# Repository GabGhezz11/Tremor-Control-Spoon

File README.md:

# Description

An electronic Tremor Control Spoon designed to compensate involuntary hand
tremors in Parkinson's disease patients during meals, developed as part of the
Biodesign course at Università Campus Bio-Medico di Roma in 2023 by a team of 10 students.

---

## Overview

This project focused on the design and development of an electronically
stabilized spoon to assist individuals with Parkinson's disease by compensating
tremors during meal consumption, promoting greater independence and comfort in
daily life. The work was developed in collaboration with a team of colleagues,
with my contribution made remotely while based in Vienna.

The device integrates mechanical, electronic, and control system design:

- **Sensing**: an IMU sensor (MPU-6050) for real-time motion tracking
  (acceleration and angular velocity)
- **Control**: an ATMega328-MUR microcontroller processes sensor data through a
  complementary filter to estimate roll and pitch angles
- **Actuation**: dual servo motors compensate roll and pitch tremors in real
  time, with compensation limited to ±30° on both axes to preserve natural
  eating motion

## Repository Structure

- `firmware/` — Arduino/C firmware implementing the sense-plan-act control loop
  - `TCS_control.ino` — main Arduino sketch
  - `Functions.c` — control and filtering functions
  - `Variables.h` — shared variable/constant definitions
- `electronics/` — PCB design and documentation (Eagle CAD)
  - `scheda_progetto_ver_4.2.sch` — schematic
  - `scheda_progetto_ver_4.2.brd` — board layout
  - `BoM_ver4.2.xlsx` — bill of materials
  - `scheda_progetto_ver_4` — project/design documentation
- `cad/` — Mechanical design files (Solid Edge/STEP) for the handle, motor
  case, and spoon tool
  - `.step Files/` — final STEP files, importable in any CAD software
  - `Drafts/` — intermediate/working Solid Edge design iterations
- `data-analysis/` — MATLAB scripts used to extract tremor frequency and
  acceleration/angular velocity ranges from a reference Parkinsonian tremor
  dataset, informing sensor and motor specifications

## Design Highlights

**Mechanical**: modeled in Solid Edge and based on anthropometric hand data
from adult users, optimized for usability, compactness, and dishwasher-safe
cleaning. Made of polypropylene (biocompatible, heat-resistant, dishwasher-safe)
with silicon caps for the removable USB/charging ports.

**Electronics**: sensing, control, and power supply modules integrated onto a
single miniaturized PCB (57 x 31 mm, a 10% area reduction from the original
demo stripboard), powered by a 2S1P LiPo battery (800 mAh, 7.4 V), with voltage
regulation and USB communication circuits.

**Firmware**: a complementary filter combines accelerometer and gyroscope data
to estimate roll and pitch angles, driving the servos to counteract tremor in
real time while allowing intentional tilting (e.g., to scoop food).

## Personal Contribution - Matlab Data Analysis

The analysis focused on two tremor-related tasks from the reference dataset:

- **Kinetic tremor (task AS316)**: analyzed to extract the acceleration and
  angular velocity ranges during a spoon-eating-like motion.
- **Postural tremor (task AS315)**: analyzed to identify the maximum and
  dominant frequencies of the Parkinsonian tremor signal.

### Scripts

| Script | Purpose |
|---|---|
| `Ranges_acc_v.mlx` | Computes the acceleration and angular velocity **ranges** (kinetic tremor, all 3 subjects, all 3 sensor locations) |
| `Dominant_freq_subj1.mlx` | Computes the **dominant frequency** of acc/gyro signals for Subject 1 (postural tremor) |
| `Dominant_freq_subj2.mlx` | Computes the **dominant frequency** of acc/gyro signals for Subject 2 (postural tremor) |
| `Dominant_freq_subj3.mlx` | Computes the **dominant frequency** of acc/gyro signals for Subject 3 (postural tremor) |
| `Dominant_freq_global.mlx` | Aggregates the dominant-frequency results of all subjects/locations and returns the global maximum |
| `Max_freq_subj1.mlx` | Computes the **maximum frequency** (95% PSD energy threshold) for Subject 1 (postural tremor) |
| `Max_freq_subj2.mlx` | Computes the **maximum frequency** (95% PSD energy threshold) for Subject 2 (postural tremor) |
| `Max_freq_subj3.mlx` | Computes the **maximum frequency** (95% PSD energy threshold) for Subject 3 (postural tremor) |
| `Max_freq_global.mlx` | Aggregates the maximum-frequency results of all subjects/locations and returns the global maximum |
| `createFit.m` | Auto-generated helper (MATLAB Distribution Fitter) used to fit a probability distribution to the angular velocity data — required by `Ranges_acc_v.mlx` |

### Methodology

**1. Signal preprocessing**
- Raw 3-axis accelerometer and gyroscope data are extracted from the dataset (`Subj{i}.off.taskASxxx.<sensor_location>.acc/.gyro`).
- A 4th-order Butterworth **high-pass filter** (cut-off 1 Hz), applied with `filtfilt` (zero-phase), removes gravity/motion bias while preserving tremor content.
- The 3-axis signals are combined into a single magnitude signal via the Euclidean norm (vector module).

**2. Frequency-domain analysis (postural tremor)**
- The **Power Spectral Density (PSD)** of the filtered signal is estimated with `periodogram`.
- **Dominant frequency**: frequency corresponding to the PSD peak.
- **Maximum frequency**: frequency below which 95% of the cumulative PSD energy is contained (computed via `trapz` on the PSD curve).
- Both metrics are computed per subject, per sensor location (index, thumb, metacarpus), and per signal type (acceleration, angular velocity), then aggregated across subjects to obtain the **global maximum/dominant frequency**, used to define the minimum IMU sampling rate (Nyquist criterion).

**3. Amplitude analysis (kinetic tremor)**
- Acceleration and angular velocity magnitudes are pooled across all subjects and sensor locations.
- A **kernel density estimate** (`ksdensity`, positive support) is computed for both signals.
- The upper bound of the working range is defined as the value below which 95% of the cumulative probability density falls; the range is then obtained by mirroring this value onto the negative axis (assuming symmetric bidirectional motion).
- The result is cross-checked against the 95th percentile/quantile of the raw pooled data (`quantile`, `prctile`) as a validation step.
- `createFit.m` is used to verify that the angular velocity distribution is **not normal**, justifying the use of the empirical (KDE-based) approach instead of a parametric one.

### Outputs used for hardware design
- **Acceleration range** → used to select the IMU accelerometer full-scale range.
- **Angular velocity range** → used to select the IMU gyroscope full-scale range.
- **Global maximum/dominant frequency** → used to define the minimum IMU sampling rate (via Nyquist criterion) and to size the servo motor bandwidth/response requirements.

Results informed the electronic design directly: a maximum signal frequency of 42 Hz and dominant frequency of 12.3 Hz were used to set the IMU sampling rate
(respecting the Nyquist theorem), while the acceleration range (±1.32 g) and angular velocity range (±4.91 rad/s) informed the sensor configuration.

## Key Results

- Compensates roll and pitch within ±30° on both axes
- Total weight: 133.4 g (spoon: 81 g)
- Overall length: 200 mm, comparable to a standard spoon
- Production cost: €69.28 (under the €100 target)
- Self-evaluation score: 34/40 across washability, safety, ergonomics and marketability criteria

## How to Use This Repository

- To review the firmware logic, see `firmware/TCS_control.ino`
- To inspect the PCB design, open the Eagle files (`.sch`/`.brd`) in `electronics/`
- To view the mechanical design, open the `.step` files inside `cad/.step Files/`
- To reproduce the tremor data analysis, open the MATLAB scripts in `data-analysis/`

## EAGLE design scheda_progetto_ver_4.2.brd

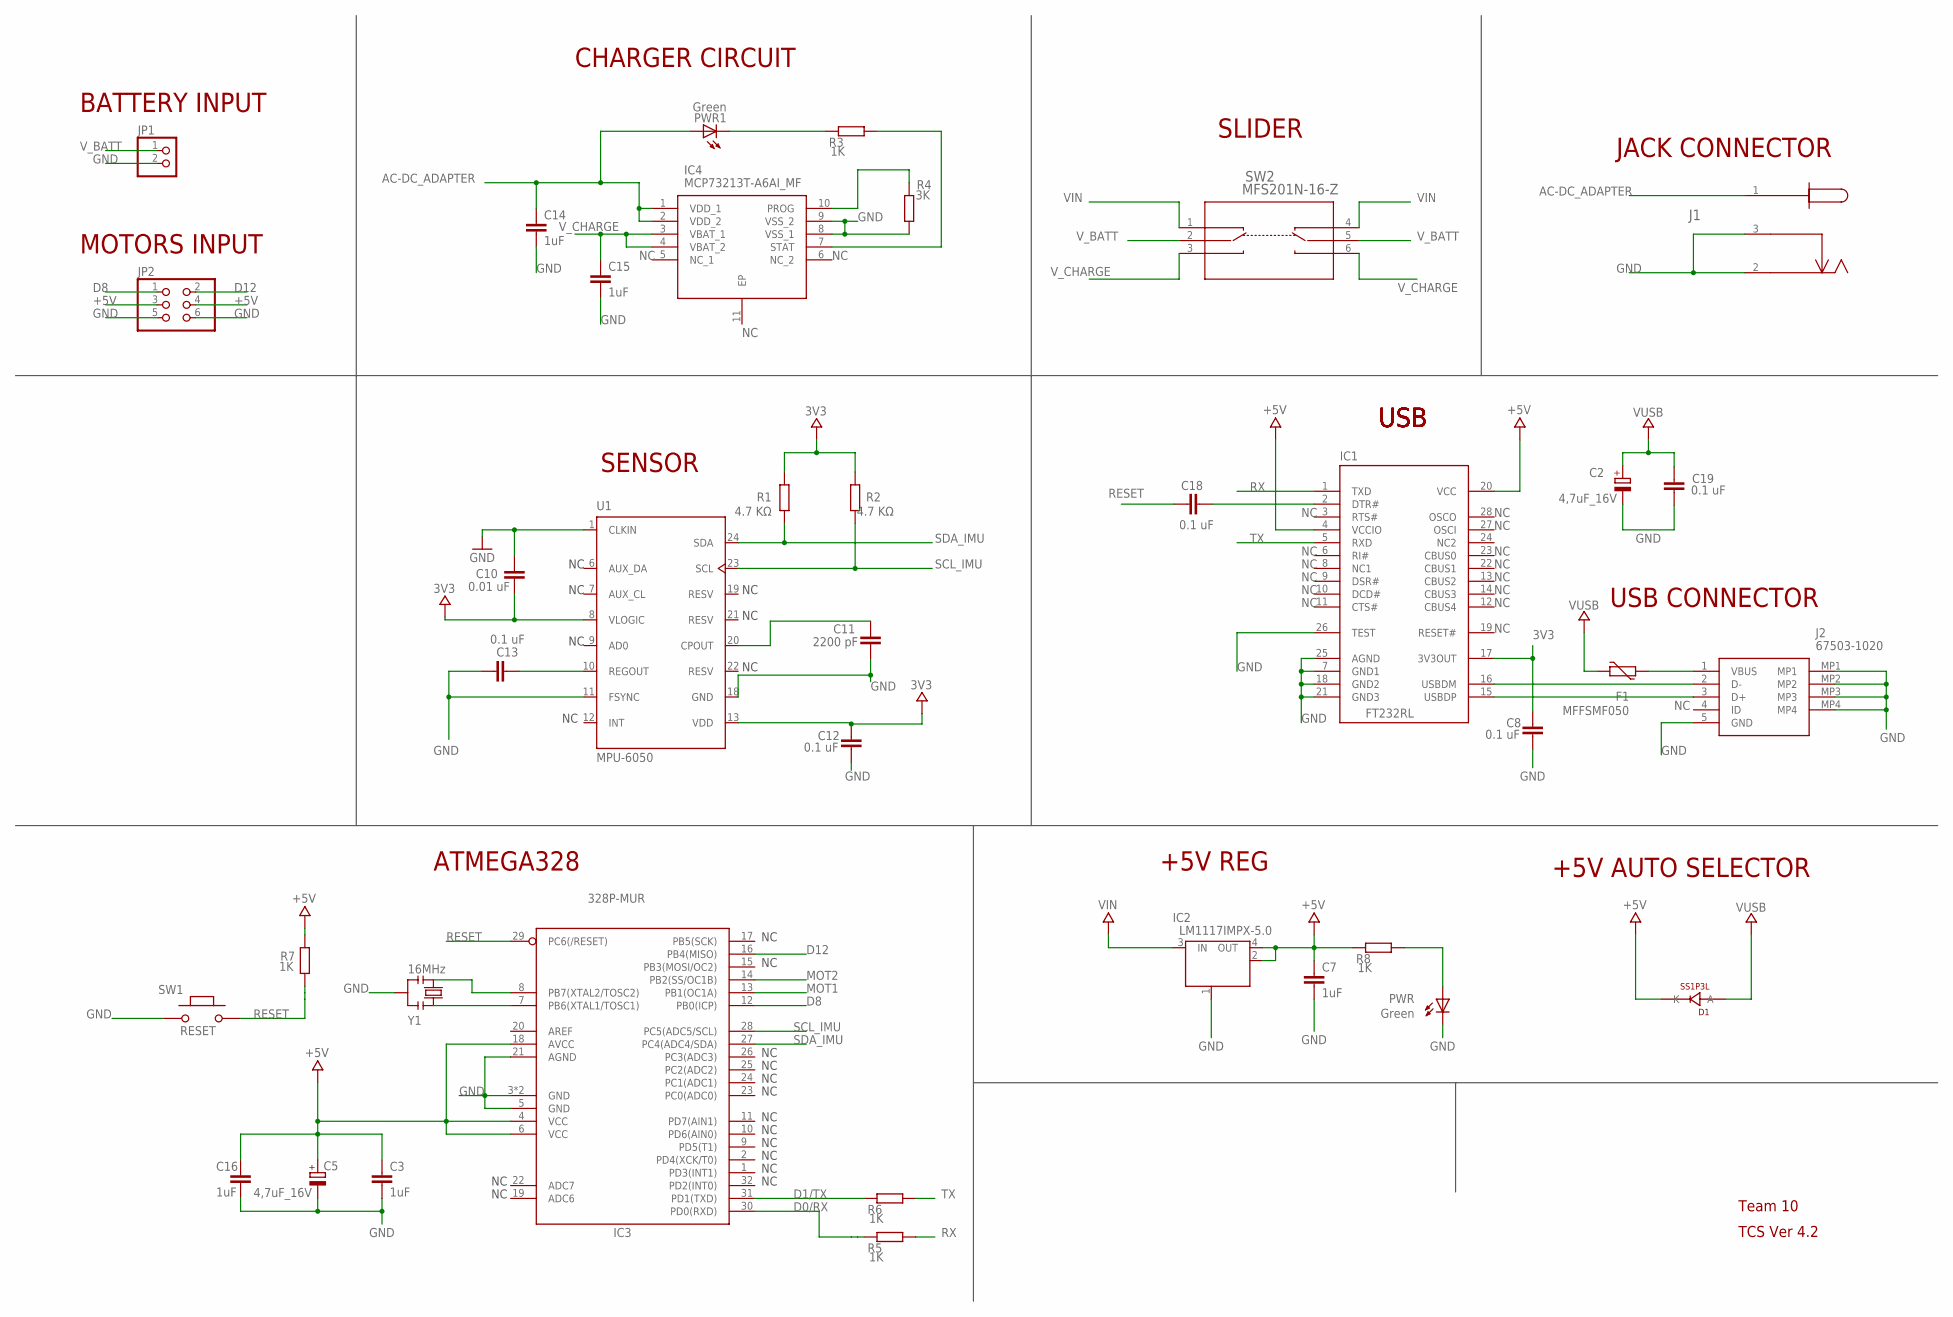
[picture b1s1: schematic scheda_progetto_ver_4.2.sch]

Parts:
C2, C5: 4,7uF_16V; TAN-A; MPN TAJA475M016RNJ
C3, C7, C14, C15, C16: 1uF; C0603; MPN 0603YC105KAT4A
C8, C12, C13, C18, C19: 0.1 uF; C0603; MPN C0603C104K3RECTU
C10: 0.01 uF; C0603; MPN GRM1885C1H103JA01D
C11: 2200 pF; C0603; MPN 885012206061
D1: SS1P3L; DO220AAL; MPN SS1P3L-M3/84A
F1: MFFSMF050; 0603-1608X90N; MPN MF-FSMF050X-2
IC1: FT232RL; SSOP28
IC2: LM1117IMPX-5.0; LINEAR_SOT223
IC3: 328P-MUR; VQFN32; MPN ATMEGA328P-MUR
IC4: MCP73213T-A6AI_MF; SON50P300X300X100-11N
J1: 694106105102; CONN3_06105102_WRE; MPN 694106105102
J2: 67503-1020; 675031020; MPN 67503-1020...
JP1: PINHD-1X2; 1X02; MPN 171826-2
JP2: PINHD-2X3; 2X03; MPN 87911-0611
PWR, PWR1: Green; CHIPLED_0805; MPN KPT-2012SGC
R1, R2: 4.7 KΩ; R0603; MPN AC0603JR-074K7L
R3, R5, R6, R7, R8: 1K; R0603; MPN CAY16-102J4LF
R4: 3K; R0603; MPN CR0603-JW-302ELF
SW1: RESET; SMD_157SW; MPN R13-24AL-05-BB
SW2: MFS201N-16-Z; MFS201N-16-Z_NDC; MPN MFS201N-16-Z
U1: MPU-6050; QFN50P400X400X95-24N; MPN MPU-6050
Y1: 16MHz; RESONATOR

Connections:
3V3: C8.2, C10.1, C12.2, IC1.17 (3V3OUT), R1.2, R2.2, U1.8 (VLOGIC), U1.13 (VDD)
+5V: C3.1, C5.1 (+), C7.1, C16.1, D1.P$1 (K), IC1.4 (VCCIO), IC1.20 (VCC), IC2.2 (OUT), IC2.4 (OUT), IC3.4 (VCC), IC3.6 (VCC), IC3.18 (AVCC), JP2.3, JP2.4, R7.2, R8.1
AC-DC_ADAPTER: C14.1, IC4.1 (VDD_1), IC4.2 (VDD_2), J1.1, PWR1.A
D0/RX: IC3.30 (PD0(RXD)), R5.1
D1/TX: IC3.31 (PD1(TXD)), R6.1
D8: IC3.12 (PB0(ICP)), JP2.1
D12: IC3.16 (PB4(MISO)), JP2.2
GND: C2.2 (-), C3.2, C5.2 (-), C7.2, C8.1, C10.2, C11.1, C12.1, C13.2, C14.2, C15.2, C16.2, C19.1, IC1.7 (GND1), IC1.18 (GND2), IC1.21 (GND3), IC1.25 (AGND), IC1.26 (TEST), IC2.1 (GND/ADJ), IC3.3 (GND), IC3.5 (GND), IC3.21 (AGND), IC3.33 (GND), IC4.8 (VSS_1), IC4.9 (VSS_2), J1.2, J1.3, J2.5 (GND), J2.MP1, J2.MP2, J2.MP3, J2.MP4, JP1.2, JP2.5, JP2.6, PWR.C, R4.2, SW1.1, U1.1 (CLKIN), U1.11 (FSYNC), U1.18 (GND), Y1.2
MOT1: IC3.13 (PB1(OC1A))
MOT2: IC3.14 (PB2(SS/OC1B))
unnamed: IC3.8 (PB7(XTAL2/TOSC2)), Y1.3
unnamed: IC3.7 (PB6(XTAL1/TOSC1)), Y1.1
unnamed: PWR.A, R8.2
unnamed: C18.1, IC1.2 (DTR#)
unnamed: IC1.15 (USBDP), J2.3 (D+)
unnamed: IC1.16 (USBDM), J2.2 (D-)
unnamed: C11.2, U1.20 (CPOUT)
unnamed: IC4.10 (PROG), R4.1
unnamed: PWR1.C, R3.1
unnamed: IC4.7 (STAT), R3.2
unnamed: C13.1, U1.10 (REGOUT)
unnamed: F1.2, J2.1 (VBUS)
RESET: C18.2, IC3.29 (PC6(/RESET)), R7.1, SW1.2
RX: IC1.1 (TXD), R5.2
SCL_IMU: IC3.28 (PC5(ADC5/SCL)), R2.1, U1.23 (SCL)
SDA_IMU: IC3.27 (PC4(ADC4/SDA)), R1.1, U1.24 (SDA)
TX: IC1.5 (RXD), R6.2
VIN: IC2.3 (IN), SW2.1, SW2.4
VUSB: C2.1 (+), C19.2, D1.P$2 (A), F1.1
V_BATT: JP1.1, SW2.2, SW2.5
V_CHARGE: C15.1, IC4.3 (VBAT_1), IC4.4 (VBAT_2), SW2.3, SW2.6

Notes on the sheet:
SENSOR
BATTERY INPUT
MOTORS INPUT
CHARGER CIRCUIT
JACK CONNECTOR
SLIDER
USB
USB CONNECTOR
+5V REG
+5V AUTO SELECTOR
Team 10
TCS Ver 4.2
ATMEGA328

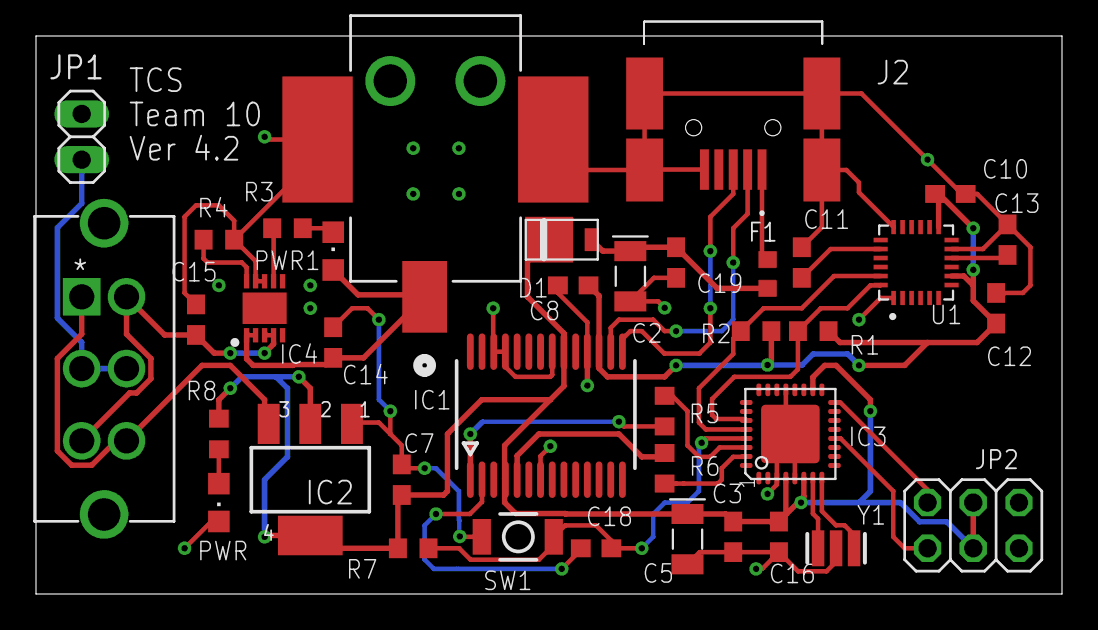
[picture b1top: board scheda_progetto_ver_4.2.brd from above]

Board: 2 copper layers, 57.0 x 31.0 mm, 38 parts (0 on the bottom side), 29 nets.

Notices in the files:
parts and their libraries:
Arduino-rcl: Copyright (c) 2016-2017 Arduino LLC.  All right reserved.
COPYRIGHT: Copyright (C) 2023 Ultra Librarian. All rights reserved.
